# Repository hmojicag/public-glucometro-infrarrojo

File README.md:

# public-glucometro-infrarrojo
Codigo, banners y documentos del glucometro infrarrojo

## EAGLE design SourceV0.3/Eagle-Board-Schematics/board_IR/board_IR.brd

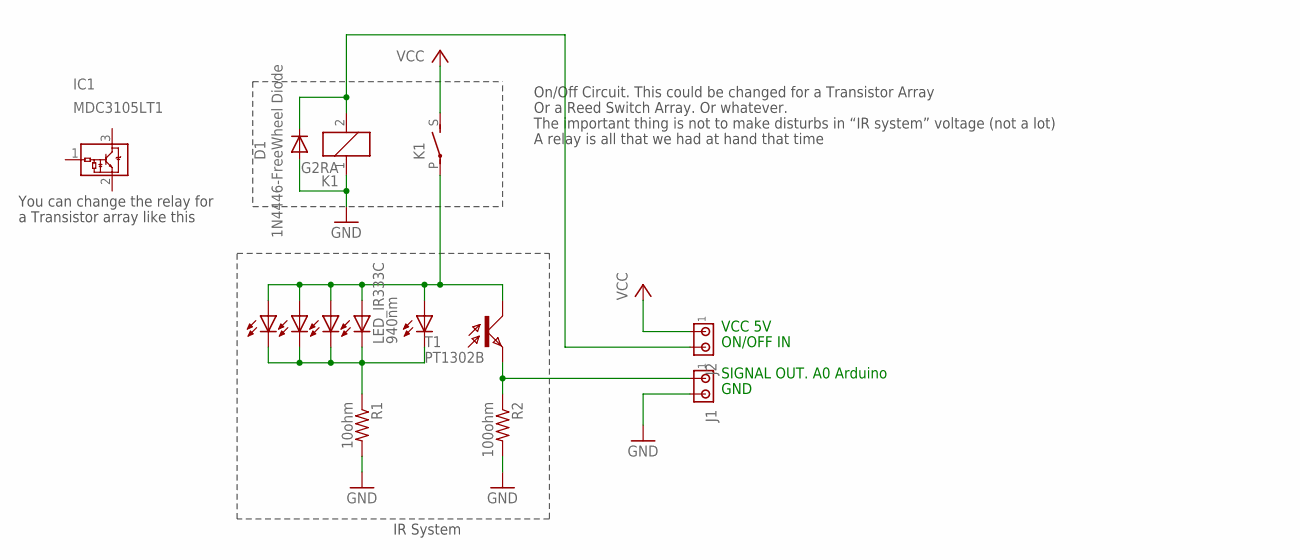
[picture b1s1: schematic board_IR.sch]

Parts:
D1: 1N4446-FreeWheel Diode; DO35-10
IC1: MDC3105LT1; SOT23
J1, J2: MTA02-156; 1X2MTA
K1: G2RA
LED_IR333C, LED_IR333C1, LED_IR333C2, LED_IR333C3, LED_IR333C4: 940nm; LED5MM
R1: 10ohm; 0204/7
R2: 100ohm; 0204/7
T1: PT1302B; LPT80A

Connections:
GND: D1.A, J1.2, K1.1, R1.2, R2.2
unnamed: LED_IR333C.K (C), LED_IR333C1.K (C), LED_IR333C2.K (C), LED_IR333C3.K (C), LED_IR333C4.K (C), R1.1
unnamed: J1.1, R2.1, T1.E
ON/OFF: D1.C, J2.2, K1.2
SWITCH: K1.P, LED_IR333C.A, LED_IR333C1.A, LED_IR333C2.A, LED_IR333C3.A, LED_IR333C4.A, T1.C
VCC: J2.1, K1.S

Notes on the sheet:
ON/OFF IN
VCC 5V
SIGNAL OUT. A0 Arduino
GND
On/Off Circuit. This could be changed for a Transistor Array
A relay is all that we had at hand that time
Or a Reed Switch Array. Or whatever.
The important thing is not to make disturbs in “IR system” voltage (not a lot)
You can change the relay for
a Transistor array like this
IR System

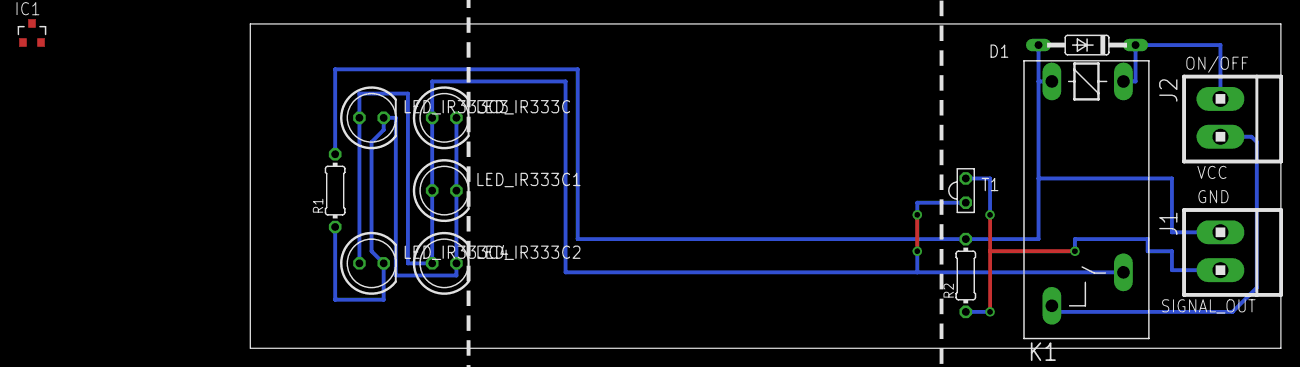
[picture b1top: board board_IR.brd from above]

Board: 2 copper layers, 107.9 x 34.0 mm, 13 parts (0 on the bottom side), 6 nets.

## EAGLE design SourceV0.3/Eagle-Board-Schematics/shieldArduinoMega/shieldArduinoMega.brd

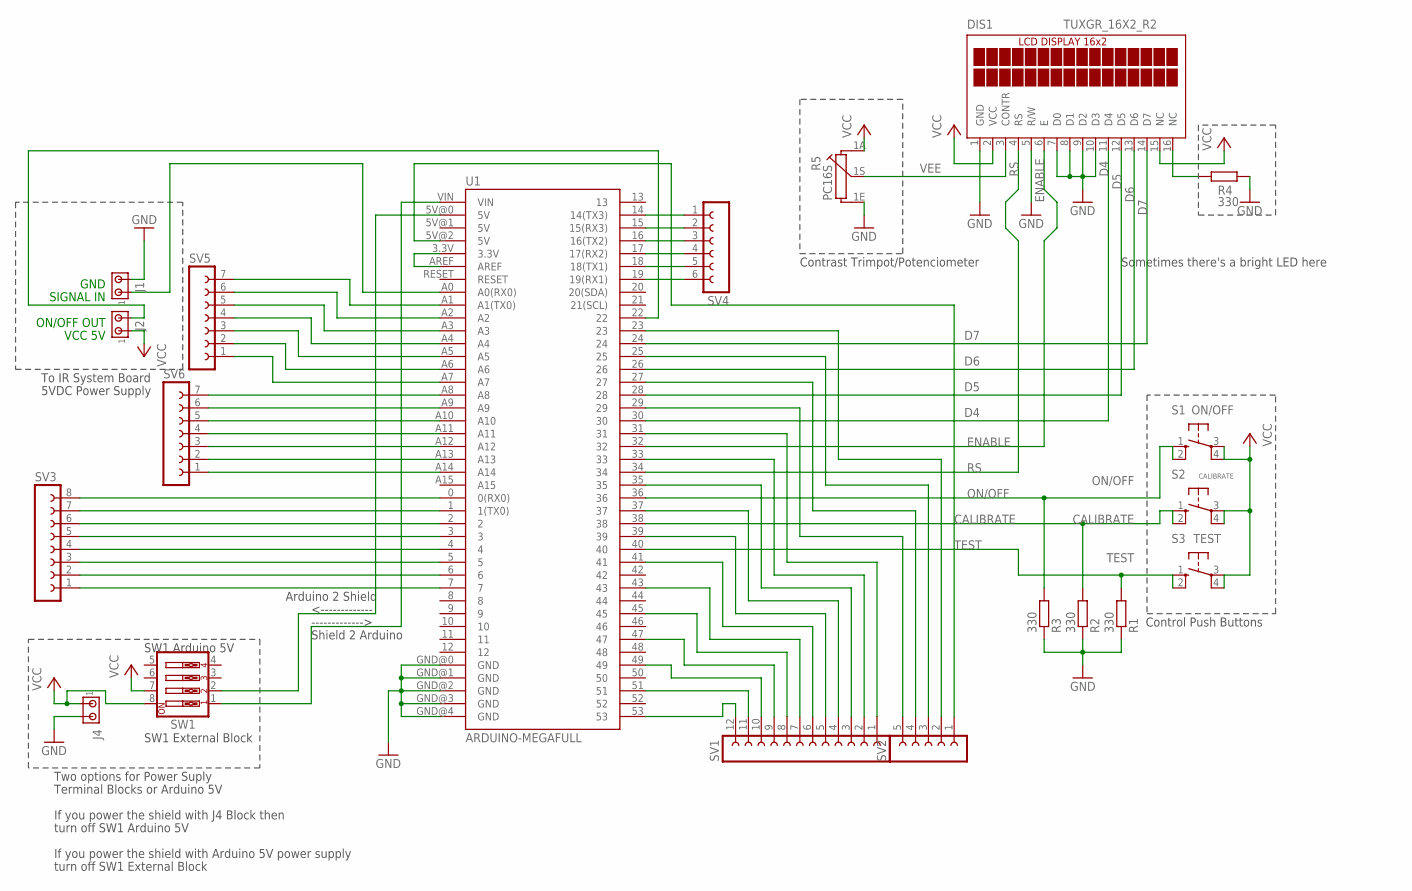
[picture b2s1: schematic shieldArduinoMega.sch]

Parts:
DIS1: TUXGR_16X2_R2
J1, J2, J4: MTA02-156; 1X2MTA
R1, R2, R3, R4: 330; 0204/7
R5: PC16S
S1: ON/OFF; B3F-10XX
S2: CALIBRATE; B3F-10XX
S3: TEST; B3F-10XX
SV1: FE12-1; FE12
SV2: FE05-1
SV3: FE08-1; FE08
SV4: FE06-1; FE06
SV5, SV6: FE07-1; FE07
SW1: SW_DIP-4; EDG-04
U1: ARDUINO-MEGAFULL; ARDUINO_MEGA

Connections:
3.3: U1.3.3V, U1.AREF
CALIBRATE: R2.2, S2.1 (S), S2.2 (S1), U1.38
D4: DIS1.11 (D4), U1.30
D5: DIS1.12 (D5), U1.28
D6: DIS1.13 (D6), U1.26
D7: DIS1.14 (D7), U1.24
ENABLE: DIS1.6 (E), U1.32
GND: DIS1.1 (GND), DIS1.5 (R/W), DIS1.7 (D0), DIS1.8 (D1), DIS1.9 (D2), DIS1.10 (D3), J1.2, J4.2, R1.1, R2.1, R3.1, R4.2, R5.1E, U1.GND@0 (GND), U1.GND@1 (GND), U1.GND@2 (GND), U1.GND@3 (GND), U1.GND@4 (GND)
IR_ON/OFF: J2.2, U1.22
LED-: DIS1.16 (NC), R4.1
unnamed: SV1.12, U1.53
unnamed: SW1.1, U1.VIN
unnamed: SV1.11, U1.51
unnamed: SW1.2, U1.5V@0 (5V)
unnamed: SV1.10, U1.49
unnamed: SV1.9, U1.47
unnamed: SV1.8, U1.45
unnamed: SV1.7, U1.43
unnamed: SV1.6, U1.41
unnamed: SV1.5, U1.39
unnamed: SV1.4, U1.37
unnamed: SV1.3, U1.35
unnamed: SV1.2, U1.33
unnamed: SV1.1, U1.31
unnamed: SV2.5, U1.29
unnamed: SV2.4, U1.27
unnamed: SV2.3, U1.25
unnamed: SV2.2, U1.23
unnamed: SV2.1, U1.5V@2 (5V)
unnamed: SV3.8, U1.0 (0(RX0))
unnamed: SV3.7, U1.1 (1(TX0))
unnamed: SV3.6, U1.2
unnamed: SV3.5, U1.3
unnamed: SV3.4, U1.4
unnamed: SV3.3, U1.5
unnamed: SV3.2, U1.6
unnamed: SV3.1, U1.7
unnamed: SV4.1, U1.14 (14(TX3))
unnamed: SV4.2, U1.15 (15(RX3))
unnamed: SV4.3, U1.16 (16(TX2))
unnamed: SV4.4, U1.17 (17(RX2))
unnamed: SV4.5, U1.18 (18(TX1))
unnamed: SV4.6, U1.19 (19(RX1))
unnamed: SV5.7, U1.A1 (A1(TX0))
unnamed: SV5.6, U1.A2
unnamed: SV5.5, U1.A3
unnamed: SV5.4, U1.A4
unnamed: SV5.3, U1.A5
unnamed: SV5.2, U1.A6
unnamed: SV5.1, U1.A7
unnamed: SV6.7, U1.A8
unnamed: SV6.6, U1.A9
unnamed: SV6.5, U1.A10
unnamed: SV6.4, U1.A11
unnamed: SV6.3, U1.A12
unnamed: SV6.2, U1.A13
unnamed: SV6.1, U1.A14
ON/OFF: R3.2, S1.1 (S), S1.2 (S1), U1.36
RS: DIS1.4 (RS), U1.34
SIGNAL_IN: J1.1, U1.A0 (A0(RX0))
TEST: R1.2, S3.1 (S), S3.2 (S1), U1.40
VCC: DIS1.2 (VCC), DIS1.15 (NC), J2.1, J4.1, R5.1A, S1.3, S1.4 (P1), S2.3, S2.4 (P1), S3.3, S3.4 (P1), SW1.7, SW1.8
VEE: DIS1.3 (CONTR), R5.1S

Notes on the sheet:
ON/OFF OUT
VCC 5V
SIGNAL IN
GND
To IR System Board
Two options for Power Suply
5VDC Power Supply
Terminal Blocks or Arduino 5V
If you power the shield with J4 Block then
SW1 Arduino 5V
SW1 External Block
turn off SW1 Arduino 5V
If you power the shield with Arduino 5V power supply
turn off SW1 External Block
<-------------
------------->
Arduino 2 Shield
Shield 2 Arduino
Control Push Buttons
Sometimes there's a bright LED here
Contrast Trimpot/Potenciometer

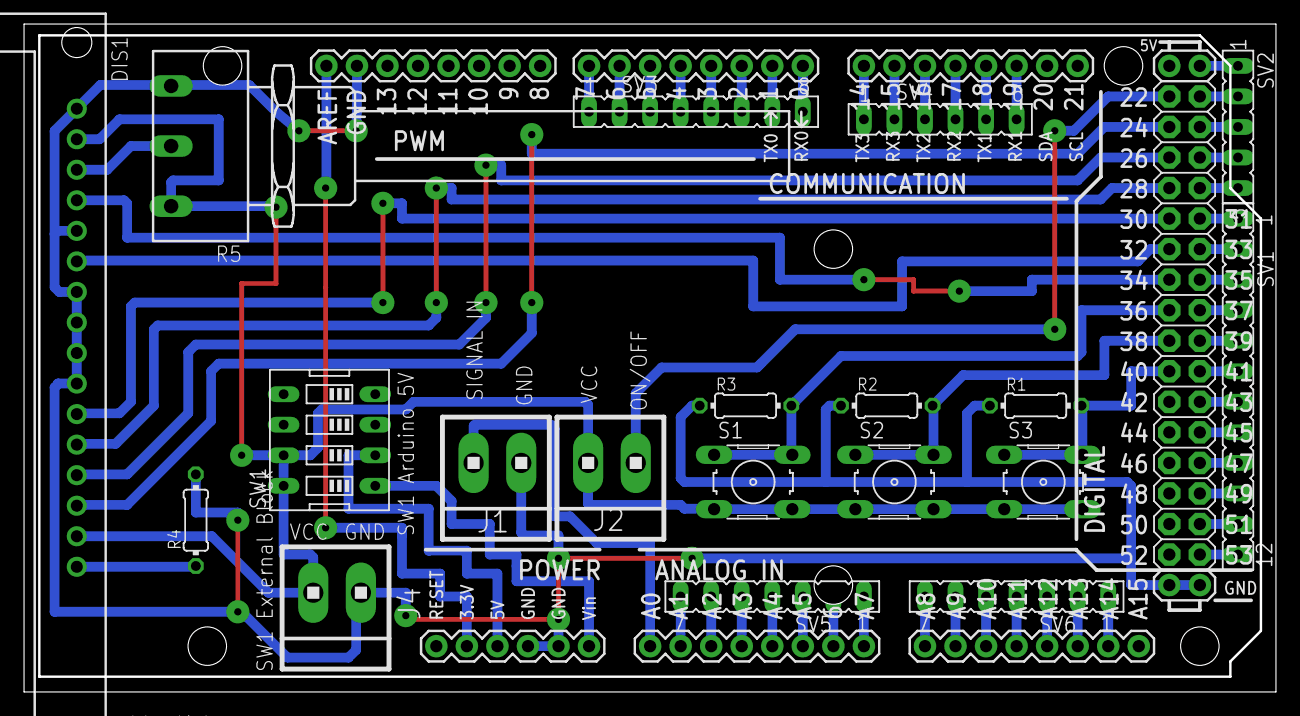
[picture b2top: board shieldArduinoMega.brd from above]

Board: 2 copper layers, 104.1 x 55.5 mm, 20 parts (0 on the bottom side), 63 nets.

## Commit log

2019-03-25 all files

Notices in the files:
parts and their libraries:
SparkFun-Boards: Licensing: CC v3.0 Share-Alike You are welcome to use this library for commercial purposes.
